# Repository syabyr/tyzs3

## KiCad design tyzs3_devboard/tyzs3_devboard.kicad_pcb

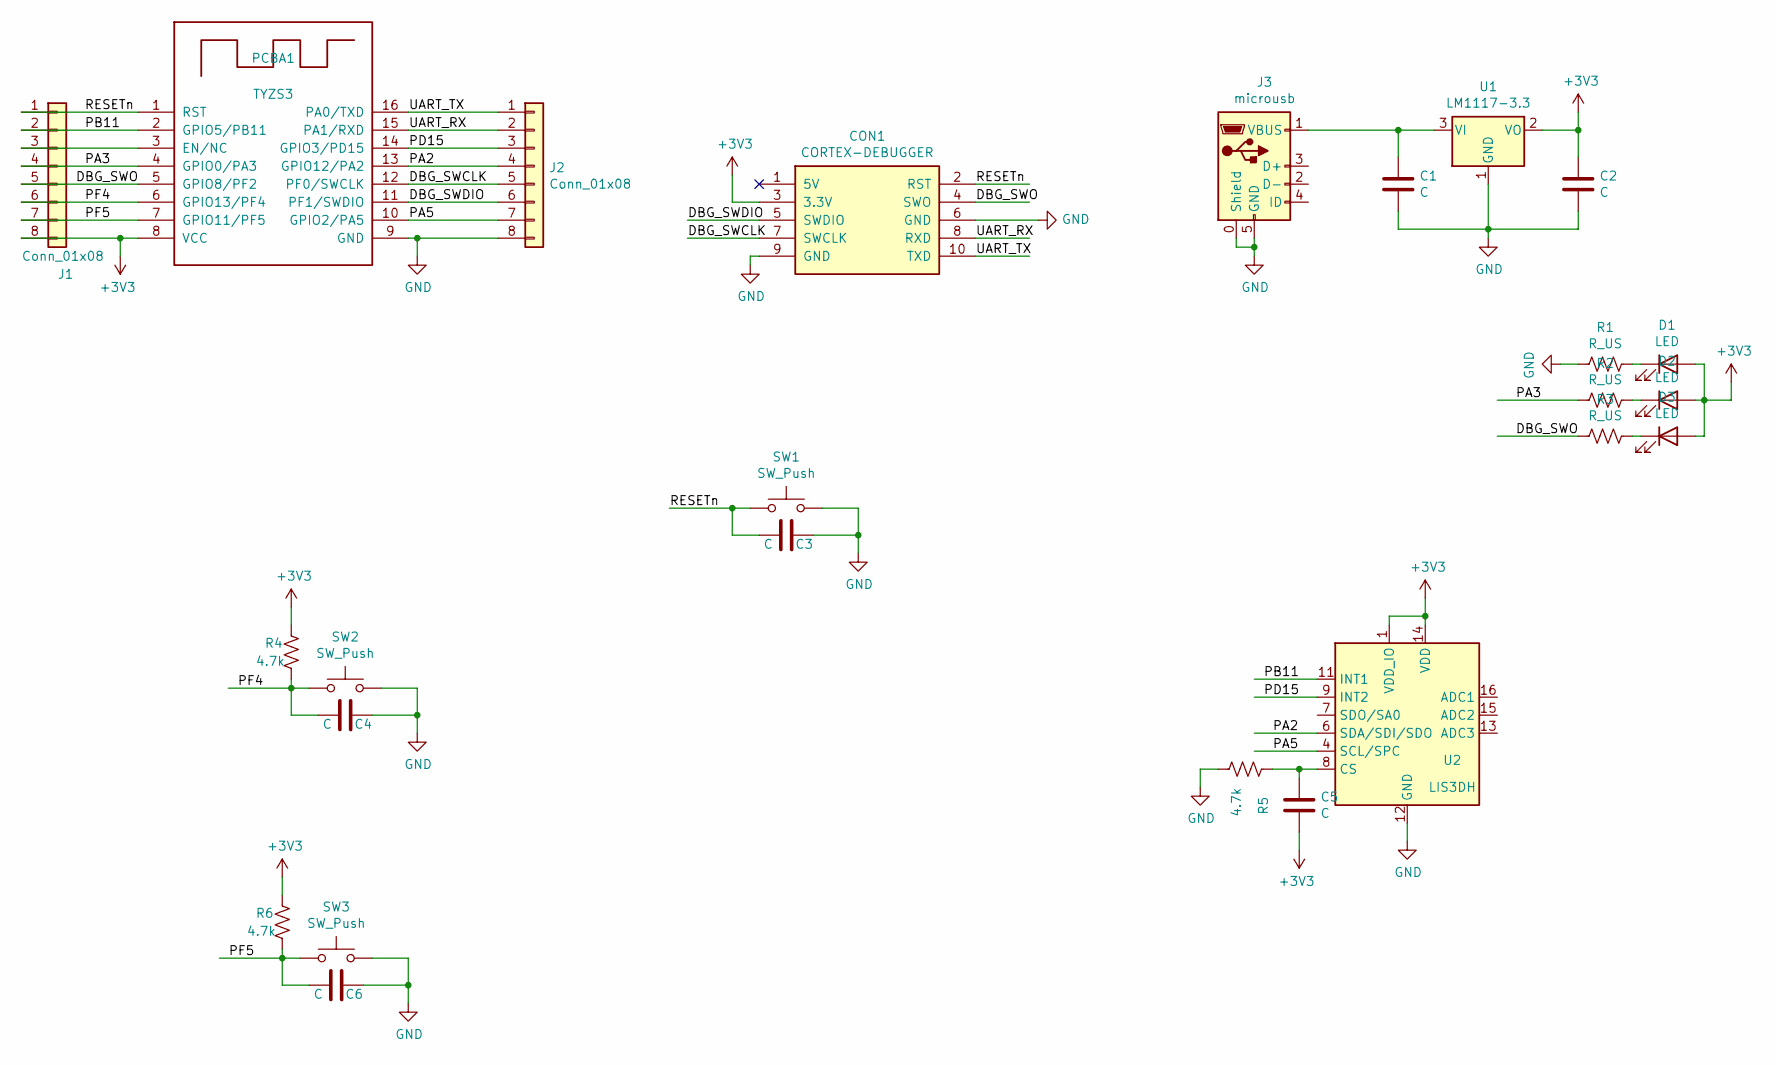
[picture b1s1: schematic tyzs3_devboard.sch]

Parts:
C1, C2: C; C_1206_3216Metric_Pad1.42x1.75mm_HandSolder
C3, C4, C5, C6: C; C_0603_1608Metric_Pad1.05x0.95mm_HandSolder
CON1: CORTEX-DEBUGGER; debugger_2x05_P1.27mm_Vertical
D1, D2, D3: LED; LED_0805_2012Metric
J1, J2: Conn_01x08; PinHeader_1x08_P2.54mm_Vertical
J3: microusb; MICRO-USB_MICRO-USB-17
PCBA1: TYZS3
R1, R2, R3: R_US; R_0603_1608Metric_Pad1.05x0.95mm_HandSolder
R4, R5, R6: 4.7k; R_0603_1608Metric_Pad1.05x0.95mm_HandSolder
SW1, SW2, SW3: SW_Push; turtlekey
U1: LM1117-3.3; SOT-223-LDO-1117LV
U2: LIS3DH; LGA-16_3x3mm_P0.5mm_LayoutBorder3x5y

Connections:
+3V3: C2.1, C5.2, CON1.3 (3.3V), D1.2 (A), D2.2 (A), D3.2 (A), J1.8, PCBA1.8 (VCC), R4.1, R6.1, U1.2 (VO), U2.1 (VDD_IO), U2.14 (VDD)
/DBG_SWCLK: CON1.7 (SWCLK), J2.5, PCBA1.12 (PF0/SWCLK)
/DBG_SWDIO: CON1.5 (SWDIO), J2.6, PCBA1.11 (PF1/SWDIO)
/DBG_SWO: CON1.4 (SWO), J1.5, PCBA1.5 (GPIO8/PF2), R3.2
/PA2: J2.4, PCBA1.13 (GPIO12/PA2), U2.6 (SDA/SDI/SDO)
/PA3: J1.4, PCBA1.4 (GPIO0/PA3), R2.2
/PA5: J2.7, PCBA1.10 (GPIO2/PA5), U2.4 (SCL/SPC)
/PB11: J1.2, PCBA1.2 (GPIO5/PB11), U2.11 (INT1)
/PD15: J2.3, PCBA1.14 (GPIO3/PD15), U2.9 (INT2)
/PF4: C4.2, J1.6, PCBA1.6 (GPIO13/PF4), R4.2, SW2.1
/PF5: C6.2, J1.7, PCBA1.7 (GPIO11/PF5), R6.2, SW3.1
/RESETn: C3.2, CON1.2 (RST), J1.1, PCBA1.1 (RST), SW1.1
/UART_RX: CON1.8 (RXD), J2.2, PCBA1.15 (PA1/RXD)
/UART_TX: CON1.10 (TXD), J2.1, PCBA1.16 (PA0/TXD)
GND: C1.2, C2.2, C3.1, C4.1, C6.1, CON1.6 (GND), CON1.9 (GND), J2.8, J3.0 (Shield), J3.5 (GND), PCBA1.9 (GND), R1.2, R5.2, SW1.2, SW2.2, SW3.2, U1.1 (GND), U2.5 (GND), U2.10 (GND), U2.12 (GND)
unnamed: C1.1, J3.1 (VBUS), U1.3 (VI)
unnamed: C5.1, R5.1, U2.8 (CS)
unnamed: D1.1 (K), R1.1
unnamed: D2.1 (K), R2.1
unnamed: D3.1 (K), R3.1
unnamed: J1.3, PCBA1.3 (EN/NC)

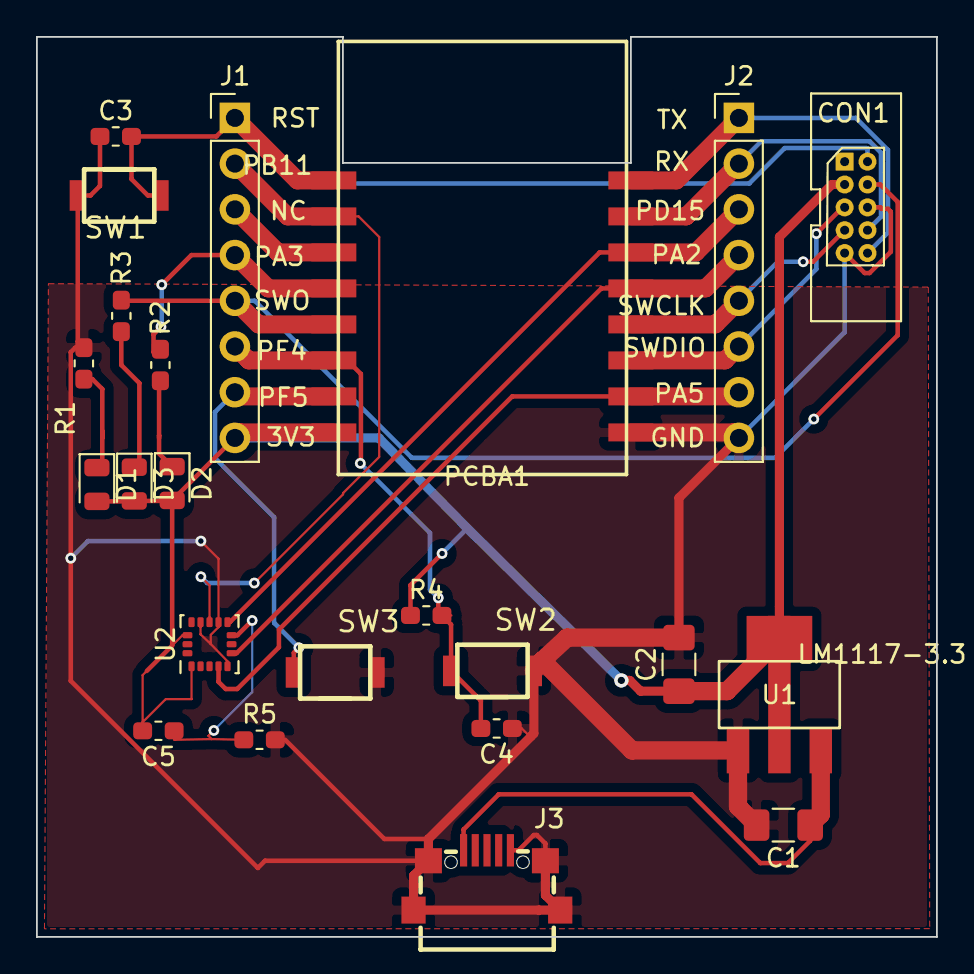
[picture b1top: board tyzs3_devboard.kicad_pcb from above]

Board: 2 copper layers, 50.0 x 50.0 mm, 23 parts (0 on the bottom side), 21 nets.

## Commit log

2021-06-06 devboaord
